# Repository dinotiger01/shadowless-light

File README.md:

# shadowless-light
## if you are a Stardance reviewer i messed up when doing the ship it has the wrong banner and video

***
## description
demo video: https://youtu.be/H-r51vnOVfs<br>
this is a desk light designed to not cast a shadow to make working on fine details easier<br>
it works by having a main light then there is octogon ring around it that has lights and will tilt in and out to make sure every spot has at least one light on it<br>

| regular light                                      | shadowless ligh                                                       |
|----------------------------------------------------|-----------------------------------------------------------------------|
|  |  

### use cases
* soldering
* painting fine detail
* just like any kinda of work tbh
### features
* btight
* RGBW
* UV
* adjustable lights
* blind yourself
## assembly
i cover this in the yt video a lot better
***
### 3d print
settings:<br>
plastic: pla<br>
supports: trees<br>
layer hight: 0.28mm<br>
nozzle: 0.4mm<br>
nozzle temp: 210°C<br>
bed temp: 60°C<br>
infill: 15%<br>

| number | name|
| -------- | ------- |
| 1 | hook |
| 1 | main |
| 16 | supports |
| 8 | light |
| 8 | pivoit |
| 8 | push |
| 4 | servo |
| 16 | pin |
| 1 | cover |
### wall 
attatch the stand to the wall the instructions are on the box
### 3d print assembly
* remove suports
* put the hook on stand
* place the main thing on the hook
* place all the 16 suports in the main thing and secure it with the pins
* thread the pivots throught the suports and the lights to make an octogon
* put the servos through the big holes in the main thing
* then thread the push through the top of the light and the servo
* then the goes on top of the main thing
### pcbs
| number | name        |
|--------|-------------|
| 8      | left wing   |
| 8      | right wing  |
| 1      | main        |
| 1      | indicator   |
| 1      | motherboard |
### soldering 
350 c recomended
* solder the 1 left wing light
* solder the 1 right wing light
* use the pad on the side to hold them togeather
* solder wires to the sides of the pcb
* repeate x 8
* main board
  * RGBW the uv 
  * one of the lights needs some help
* mother board 
  * the v line is a cut power cable
* indicator
### arduino
you need to use adruino ide to upload the script to the arduino nano
### servos :(
so i forgot about the servo when making the pcb so there isnt a convinent break out for it so
you need to solder a wire to pin 7 directly then split the wire in to 4 then thats the data wire for the servos and the gnd and power come direcly from the power suply
also i think my servos are too weak so they wernt able to actualy do anyyhing
### assembling electronics
* wings
  * zip tie just like every thing
  * then do that 8 times
* main
  * you guesed it zip ties
* plug in all the things
* power supply
  * connect a 120v ac up to the main thing
  * connect one side to the switch on the front and the other side to one on the things on the 12v rectifer
  * this is another thing i forgot to add to the pcb connect the 12v output to the power wires on the mother board
  * now for the 5v if you have a buck dc to dc converter use that i didnt so i did this
  * connect a wall 5v rectifyer in parralel with the 120vac then plug that in to the the arduino with a usb to usbc
  * however we need to cut this wire then split it in to a bunch of things so that we can power the servos
## documantation
* schemadic 
  * indicator this is used to show if it is on and what value you are adjusting
  * 
  * right wing 
  * 
  * 
  * left wing
  * 
  * 
  * motherboard
  * 
  * 
  * main
  * 
  * 
* voltage stuff
  * lights are running at 12v 
  * each light runs at 20mA there is 4 lights in eash light there are 101 lights so 404 individual light + the 20 uv lights all run at 20mA or 0.02A * 424 = 8.48A
  * the 12 has 10A to cover it all
* lumins alot
  * red 4.8 lumens
  * green 10.7 lumens
  * blue 2.2 lumens
  * 10.7 lumens
  * 28.4 lumens per light X 101 = 248.4 lumens at max britness 
* it is suposed to sit about 600mm off your desk
* its about 600mm in total witch ngl i think is too big i might make a smaler one in the futger
## extra
* i am like really bad ar soldering so like half the light dont work

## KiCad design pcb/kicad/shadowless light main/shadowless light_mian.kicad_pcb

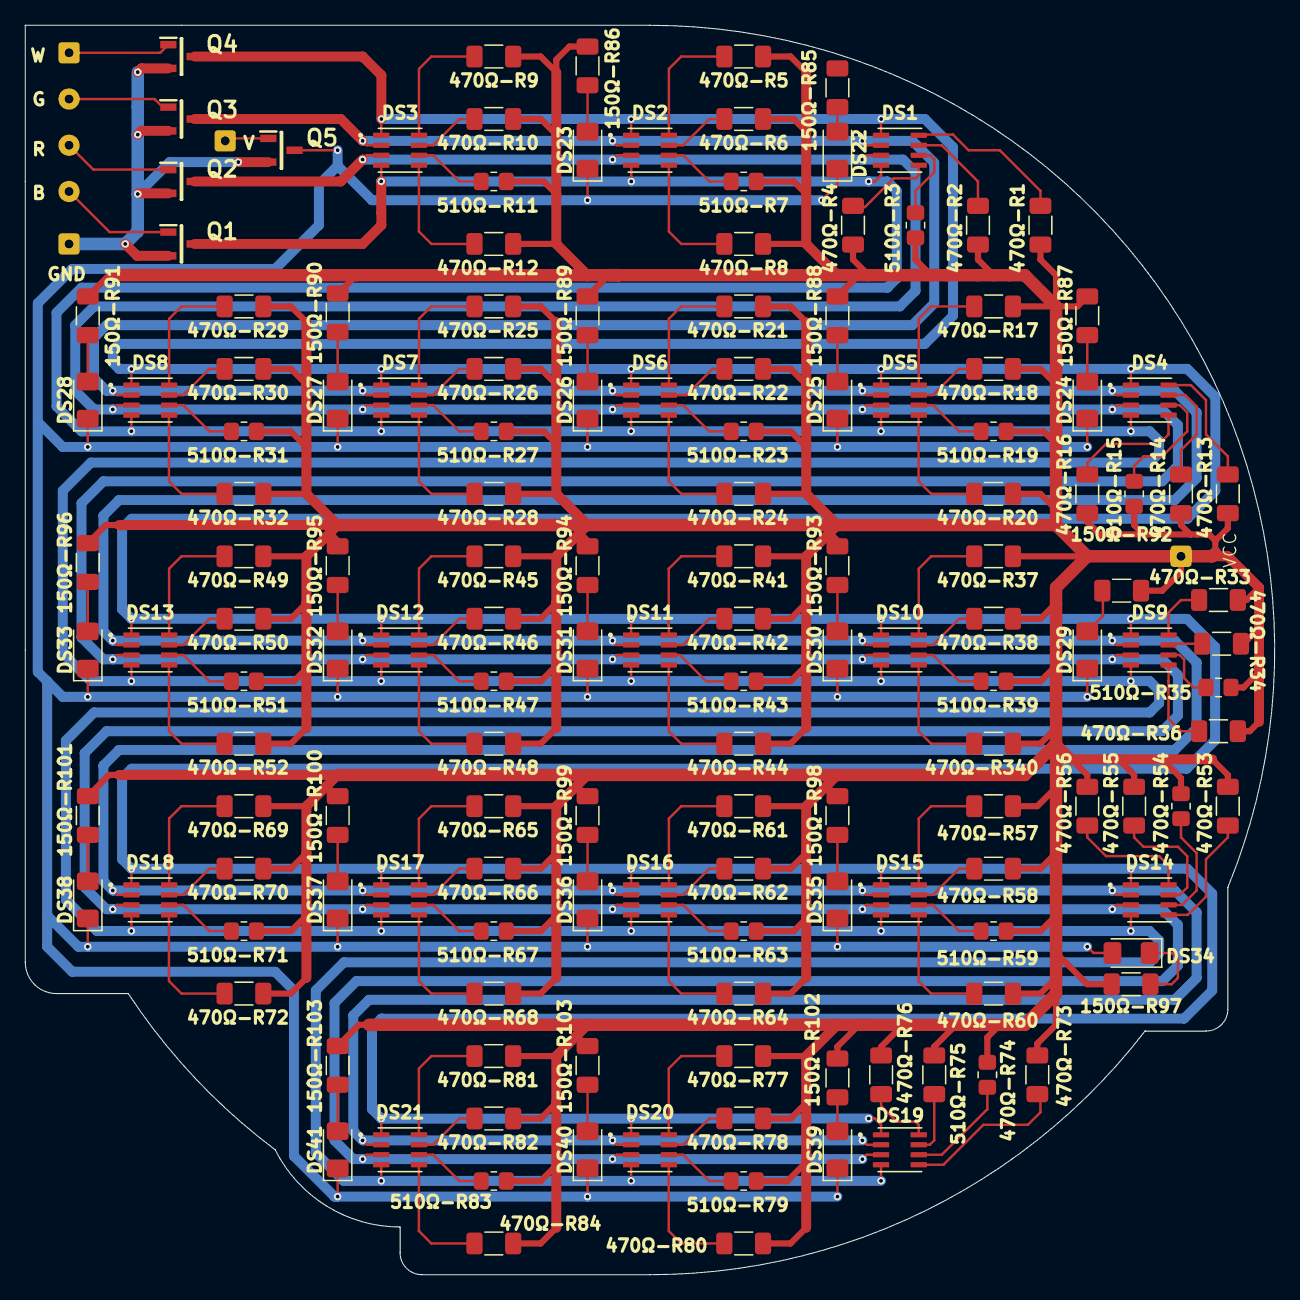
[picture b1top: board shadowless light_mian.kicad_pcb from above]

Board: 2 copper layers, 100.0 x 100.0 mm, 65 parts (0 on the bottom side), 11 nets.

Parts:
150Ω-R85, 150Ω-R86, 150Ω-R87, 150Ω-R88, 150Ω-R89, 150Ω-R90, 150Ω-R91, 150Ω-R92, 150Ω-R93, 150Ω-R94, 150Ω-R95, 150Ω-R96, 150Ω-R97, 150Ω-R98, 150Ω-R99, 150Ω-R100, 150Ω-R101, 150Ω-R103, 150Ω-R103#2: R_1206_3216Metric_Pad1.30x1.75mm_HandSolder
DS1, DS2, DS4, DS4#2, DS5, DS6, DS7, DS8, DS11, DS11#2, DS12, DS12#2, DS13, DS15, DS16, DS17, DS17#2, DS18, DS19, DS20, DS21: LED_CLW6A-RGBW
DS22, DS23, DS24, DS25, DS26, DS27, DS28, DS29, DS30, DS31, DS32, DS33, DS34, DS35, DS36, DS37, DS38, DS39, DS40, DS41: LED_1206_3216Metric_Pad1.42x1.75mm_HandSolder
Q1, Q2, Q3, Q4, Q5: SOT95P237X112-3N

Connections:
-B: DS1.2, DS1.4, DS2.4, DS4.4, DS4#2.4, DS5.4, DS6.4, DS7.4, DS8.4, DS11.4, DS11#2.4, DS12.4, DS12#2.4, DS13.4, DS15.4, DS16.4, DS17.4, DS17#2.4, DS19.4, DS20.4, DS21.4, Q1.3
-G: DS2.2, DS4.2, DS4#2.2, DS5.2, DS6.2, DS7.2, DS8.2, DS11.2, DS11#2.2, DS12.2, DS12#2.2, DS13.2, DS15.2, DS16.2, DS17.2, DS17#2.2, DS19.2, DS20.2, DS21.2, Q3.3
-R: DS1.3, DS2.3, DS4.3, DS4#2.3, DS5.3, DS6.3, DS7.3, DS8.3, DS11.3, DS11#2.3, DS12.3, DS12#2.3, DS13.3, DS15.3, DS16.3, DS17.3, DS17#2.1, DS17#2.3, DS19.3, DS20.3, DS21.3, Q2.3
-W: DS1.1, DS2.1, DS4.1, DS4.8, DS4#2.1, DS5.1, DS6.1, DS7.1, DS8.1, DS11.1, DS11#2.1, DS12.1, DS12#2.1, DS13.1, DS15.1, DS16.1, DS17.1, DS19.1, DS20.1, DS21.1, Q4.3
B: DS1.5, DS2.5, DS4.5, DS4.7, DS4#2.5, DS5.5, DS6.5, DS7.5, DS8.5, DS11.5, DS11#2.5, DS12.5, DS12#2.5, DS15.5, DS16.5, DS17.5, DS17#2.5, DS19.5, DS20.5, DS21.5
G: DS1.7, DS2.7, DS4#2.7, DS5.7, DS6.7, DS7.7, DS8.7, DS11.7, DS11#2.7, DS12.7, DS12#2.7, DS15.7, DS16.7, DS17.7, DS17#2.7, DS19.7, DS20.7, DS21.7
GND: DS17.6, DS22.1, DS23.1, DS24.1, DS25.1, DS26.1, DS27.1, DS28.1, DS29.1, DS30.1, DS31.1, DS32.1, DS33.1, DS34.2, DS38.1, DS39.1, DS40.1, DS41.1, Q1.2, Q2.2, Q3.2, Q4.2, Q5.3
R: DS1.6, DS2.6, DS4.6, DS4#2.6, DS5.6, DS6.6, DS7.6, DS8.6, DS11.6, DS11#2.6, DS12.6, DS12#2.6, DS15.6, DS16.6, DS17#2.6, DS19.6, DS20.6, DS21.6
V: 150Ω-R85.1, 150Ω-R86.1, 150Ω-R87.1, 150Ω-R88.1, 150Ω-R89.1, 150Ω-R90.1, 150Ω-R91.1, 150Ω-R92.1, 150Ω-R93.1, 150Ω-R94.1, 150Ω-R95.1, 150Ω-R96.1, 150Ω-R97.2, 150Ω-R98.1, 150Ω-R99.1, 150Ω-R100.1, 150Ω-R101.1, 150Ω-R103.1, 150Ω-R103#2.1, DS22.2, DS23.2, DS24.2, DS25.2, DS26.2, DS27.2, DS28.2, DS29.2, DS30.2, DS31.2, DS32.2, DS33.2, DS34.1, DS35.2, DS36.2, DS37.2, DS38.2, DS39.2, DS40.2, DS41.2
VCC: 150Ω-R85.2, 150Ω-R86.2, 150Ω-R87.2, 150Ω-R88.2, 150Ω-R89.2, 150Ω-R90.2, 150Ω-R91.2, 150Ω-R92.2, 150Ω-R93.2, 150Ω-R94.2, 150Ω-R95.2, 150Ω-R96.2, 150Ω-R97.1, 150Ω-R98.2, 150Ω-R99.2, 150Ω-R100.2, 150Ω-R101.2, 150Ω-R103.2, 150Ω-R103#2.2, DS21.8, Q1.1, Q2.1, Q3.1
W: DS1.8, DS2.8, DS4#2.8, DS5.8, DS6.8, DS7.8, DS8.8, DS11.8, DS11#2.8, DS12.8, DS12#2.8, DS15.8, DS16.8, DS17.8, DS17#2.8, DS19.8, DS20.8

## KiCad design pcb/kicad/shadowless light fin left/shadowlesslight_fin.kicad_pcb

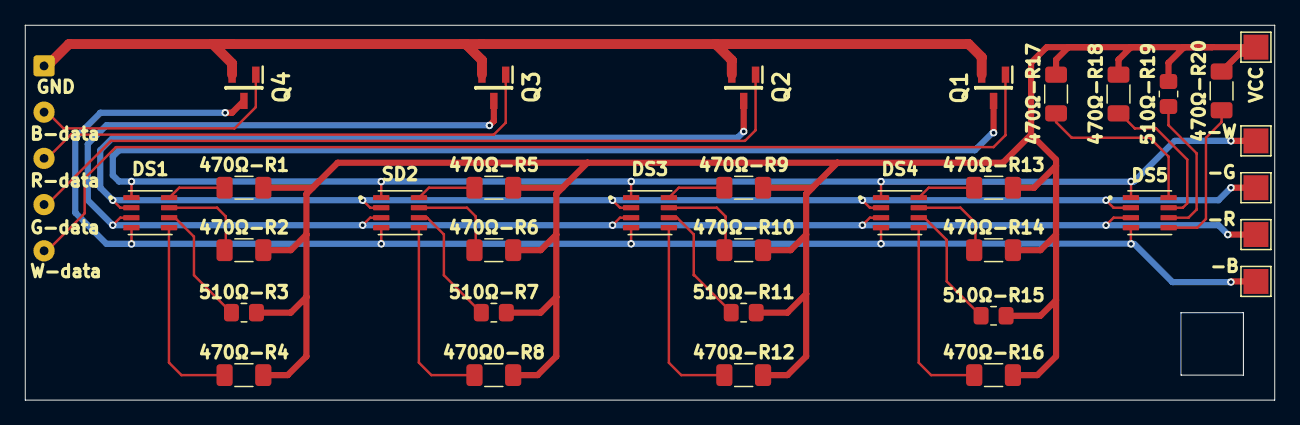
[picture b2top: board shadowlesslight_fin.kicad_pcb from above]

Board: 2 copper layers, 100.0 x 30.0 mm, 34 parts (0 on the bottom side), 10 nets.

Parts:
470Ω0-R8, 470Ω-R1, 470Ω-R2, 470Ω-R4, 470Ω-R5, 470Ω-R6, 470Ω-R9, 470Ω-R10, 470Ω-R12, 470Ω-R13, 470Ω-R14, 470Ω-R16, 470Ω-R17, 470Ω-R18, 470Ω-R20: R_1206_3216Metric_Pad1.30x1.75mm_HandSolder
510Ω-R3, 510Ω-R7, 510Ω-R11, 510Ω-R15, 510Ω-R19: R_0805_2012Metric_Pad1.20x1.40mm_HandSolder
-B: TestPoint_Pad_2.0x2.0mm
-G: TestPoint_Pad_2.0x2.0mm
-R: TestPoint_Pad_2.0x2.0mm
-W: TestPoint_Pad_2.0x2.0mm
DS1, DS3, DS4, DS5: LED_CLW6A_RGBW
Q1, Q2, Q3, Q4: SOT95P237X112-3N
SD2: LED_CLW6A_RGBW
VCC: TestPoint_Pad_2.0x2.0mm

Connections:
-B: -B.1, DS1.4, DS3.4, DS4.4, DS5.4, Q4.3, SD2.4
-G: -G.1, DS1.2, DS3.2, DS4.2, DS5.2, Q2.3, SD2.2
-R: -R.1, DS1.3, DS3.3, DS4.3, DS5.3, Q3.3, SD2.3
-w: -W.1, DS1.1, DS3.1, DS4.1, DS5.1, Q1.3, SD2.1
B: 470Ω-R20.1, DS1.5, DS3.5, DS4.5, DS5.5, SD2.5
G: 470Ω-R18.1, DS1.7, DS3.7, DS4.7, DS5.7, SD2.7
GND: Q1.2, Q2.2, Q3.2, Q4.2
R: DS1.6, DS3.6, DS4.6, DS5.6, SD2.6
VCC: 470Ω-R17.2, 470Ω-R18.2, 470Ω-R20.2, VCC.1
W: 470Ω-R17.1, DS1.8, DS3.8, DS4.8, DS5.8, SD2.8

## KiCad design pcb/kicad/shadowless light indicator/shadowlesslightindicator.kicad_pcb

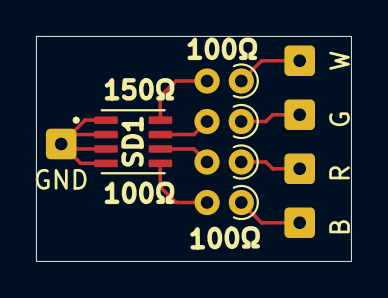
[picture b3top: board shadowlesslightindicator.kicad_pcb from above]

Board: 2 copper layers, 17.5 x 12.5 mm, 10 parts (0 on the bottom side), 5 nets.

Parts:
100Ω, 100Ω#2, 100Ω#3, 150Ω: R_Axial_DIN0204_L3.6mm_D1.6mm_P1.90mm_Vertical
B: SolderWire-0.127sqmm_1x01_D0.48mm_OD1mm
G: SolderWire-0.127sqmm_1x01_D0.48mm_OD1mm
GND: SolderWire-0.127sqmm_1x01_D0.48mm_OD1mm
R: SolderWire-0.127sqmm_1x01_D0.48mm_OD1mm
SD1: LED_CLW6A_RGBW
W: SolderWire-0.127sqmm_1x01_D0.48mm_OD1mm

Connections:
B: 100Ω#2.1, 100Ω#2.2, SD1.5, W.1
G: 150Ω.1, 150Ω.2, R.1, SD1.7
GND: GND.1, SD1.1, SD1.2, SD1.3, SD1.4
R: 100Ω.1, 100Ω.2, G.1, SD1.6
W: 100Ω#3.1, 100Ω#3.2, B.1, SD1.8
